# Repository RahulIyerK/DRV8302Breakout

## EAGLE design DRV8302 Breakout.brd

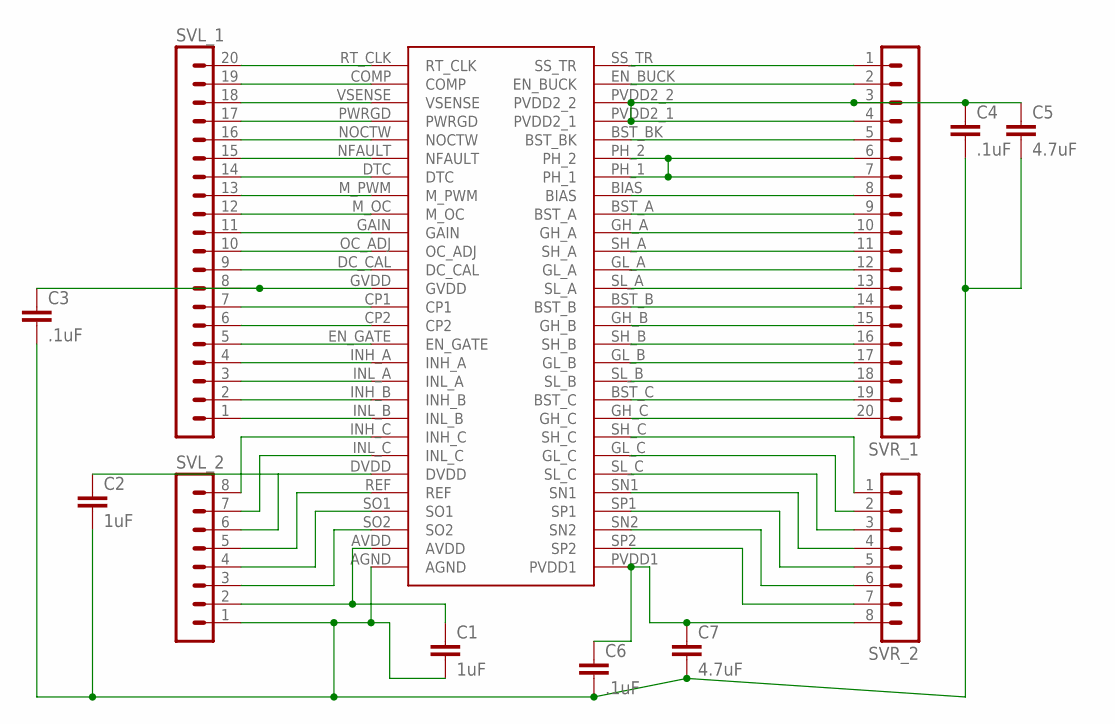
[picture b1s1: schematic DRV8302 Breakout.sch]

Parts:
C1, C2: 1uF; C0603
C3, C4, C6: .1uF; C0603
C5, C7: 4.7uF; C0603
IC1: DRV8302DRV8302; DRV8302
SVL_1: MA20-1
SVL_2: MA08-1
SVR_1: MA20-1
SVR_2: MA08-1

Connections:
AVDD: C1.1, IC1.AVDD, SVL_2.2
BIAS: IC1.BIAS, SVR_1.8
BST_A: IC1.BST_A, SVR_1.9
BST_BK: IC1.BST_BK, SVR_1.5
BST_C: IC1.BST_C, SVR_1.19
COMP: IC1.COMP, SVL_1.19
CP1: IC1.CP1, SVL_1.7
CP2: IC1.CP2, SVL_1.6
DC_CAL: IC1.DC_CAL, SVL_1.9
DTC: IC1.DTC, SVL_1.14
DVDD: C2.1, IC1.DVDD, SVL_2.6
EN_BUCK: IC1.EN_BUCK, SVR_1.2
EN_GATE: IC1.EN_GATE, SVL_1.5
GAIN: IC1.GAIN, SVL_1.11
GH_A: IC1.GH_A, SVR_1.10
GH_B: IC1.GH_B, SVR_1.15
GH_C: IC1.GH_C, SVR_1.20
GL_A: IC1.GL_A, SVR_1.12
GL_B: IC1.GL_B, SVR_1.17
GL_C: IC1.GL_C, SVR_2.2
GND: C1.2, C2.2, C3.2, C4.2, C5.2, C6.2, C7.2, IC1.AGND, SVL_2.1
GVDD: C3.1, IC1.GVDD, SVL_1.8
INH_A: IC1.INH_A, SVL_1.4
INH_B: IC1.INH_B, SVL_1.2
INH_C: IC1.INH_C, SVL_2.8
INL_A: IC1.INL_A, SVL_1.3
INL_B: IC1.INL_B, SVL_1.1
INL_C: IC1.INL_C, SVL_2.7
M_OC: IC1.M_OC, SVL_1.12
M_PWM: IC1.M_PWM, SVL_1.13
unnamed: IC1.SL_A, SVR_1.13
unnamed: IC1.BST_B, SVR_1.14
NFAULT: IC1.NFAULT, SVL_1.15
NOCTW: IC1.NOCTW, SVL_1.16
OC_ADJ: IC1.OC_ADJ, SVL_1.10
PH_1: IC1.PH_1, IC1.PH_2, SVR_1.6, SVR_1.7
PVDD1: C6.1, C7.1, IC1.PVDD1, SVR_2.8
PVDD2_1: C4.1, C5.1, IC1.PVDD2_1, IC1.PVDD2_2, SVR_1.3, SVR_1.4
PWRGD: IC1.PWRGD, SVL_1.17
REF: IC1.REF, SVL_2.5
RT_CLK: IC1.RT_CLK, SVL_1.20
SH_A: IC1.SH_A, SVR_1.11
SH_B: IC1.SH_B, SVR_1.16
SH_C: IC1.SH_C, SVR_2.1
SL_B: IC1.SL_B, SVR_1.18
SL_C: IC1.SL_C, SVR_2.3
SN1: IC1.SN1, SVR_2.4
SN2: IC1.SN2, SVR_2.6
SO1: IC1.SO1, SVL_2.4
SO2: IC1.SO2, SVL_2.3
SP1: IC1.SP1, SVR_2.5
SP2: IC1.SP2, SVR_2.7
SS_TR: IC1.SS_TR, SVR_1.1
VSENSE: IC1.VSENSE, SVL_1.18

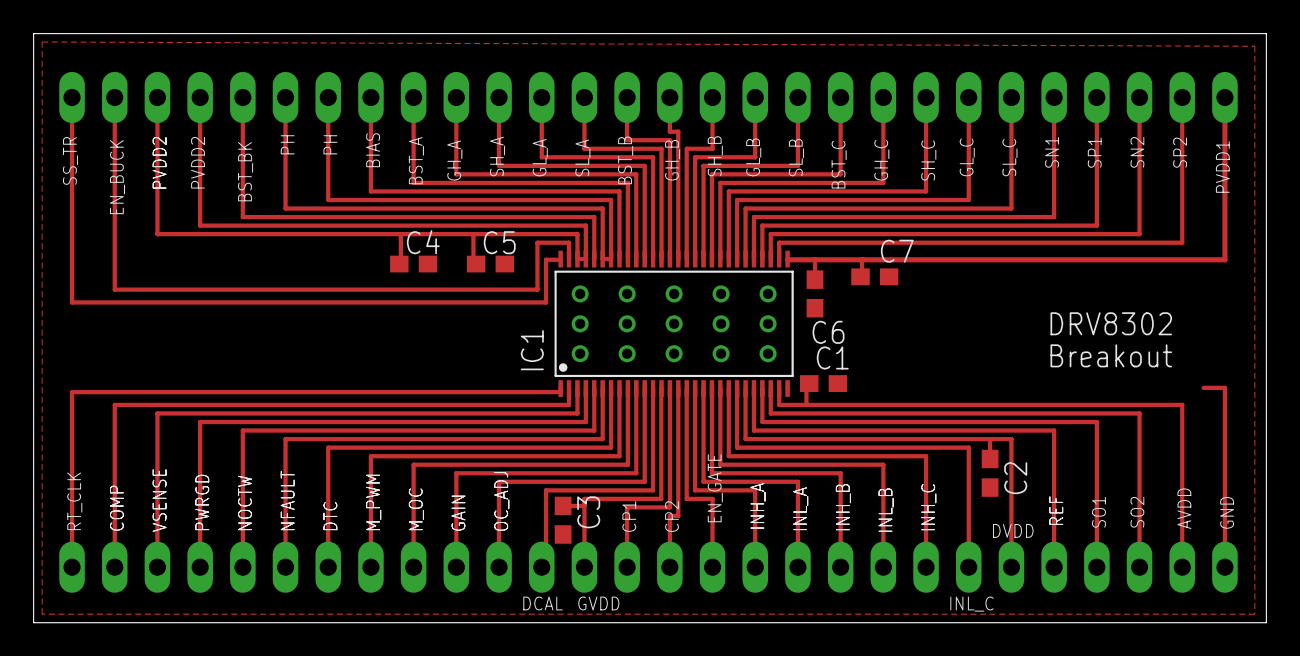
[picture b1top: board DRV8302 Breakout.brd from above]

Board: 2 copper layers, 73.3 x 35.0 mm, 12 parts (0 on the bottom side), 54 nets.

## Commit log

2016-11-18 added files for DRV8302 Breakout
